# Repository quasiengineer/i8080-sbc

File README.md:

# System board for Intel 8080
FPGA-based single board computer to run Intel 8080 CPU (up to 3.125Mhz)

## Board

Full schematics in [pdf format](./pcb/schematic.pdf)

Here is shown only main part of the board:

Archive with gerber files and drill locations could be found [here](./pcb/manufacturing.zip)

Bill of material in [CSV format](./pcb/bom.csv)

|Reference                                                                                                                           |Value               |Footprint                                                 |Mouser Part Number  |Qty|
|------------------------------------------------------------------------------------------------------------------------------------|--------------------|----------------------------------------------------------|--------------------|---|
|C1,C7,C25,C57,C62                                                                                                                   |1u                  |Capacitor_SMD:C_0805_2012Metric_Pad1.18x1.45mm_HandSolder |187-CL21B105KAFNNNG |5  |
|C2,C3,C6,C11,C12,C13,C17,C18,C19,C21,C22,C23,<br>C24,C26,C28,C29,C31,C32,C33,C34,C35,C36,C37,<br>C38,C39,C40,C41,C43,C44,C46,C48,C49,C56,C58|100n                |Capacitor_SMD:C_0805_2012Metric_Pad1.18x1.45mm_HandSolder |187-CL21B104KBCNNND |34 |
|C4,C30                                                                                                                              |4u7,4u7, low-ESR    |Capacitor_SMD:C_0805_2012Metric_Pad1.18x1.45mm_HandSolder |187-CL21A475KAQNNNE |2  |
|C5,C59,C61,C64                                                                                                                      |22u                 |Capacitor_SMD:C_0805_2012Metric_Pad1.18x1.45mm_HandSolder |187-CL21A226MAYNNNE |4  |
|C8,C9,C10,C55                                                                                                                       |10u,10u, low-ESR    |Capacitor_SMD:C_0805_2012Metric_Pad1.18x1.45mm_HandSolder |187-CL21A106KAYNNNF |4  |
|C20,C27                                                                                                                             |10p                 |Capacitor_SMD:C_0805_2012Metric_Pad1.18x1.45mm_HandSolder |710-885012007051    |2  |
|C42,C45                                                                                                                             |10p                 |Capacitor_SMD:C_0402_1005Metric_Pad0.74x0.62mm_HandSolder |603-CC402JRNPO8BN100|2  |
|C60                                                                                                                                 |33p                 |Capacitor_SMD:C_0805_2012Metric_Pad1.18x1.45mm_HandSolder |710-885012007031    |1  |
|C63                                                                                                                                 |22p                 |Capacitor_SMD:C_0805_2012Metric_Pad1.18x1.45mm_HandSolder |710-885012007053    |1  |
|D1                                                                                                                                  |Red                 |LED_SMD:LED_0805_2012Metric_Pad1.15x1.40mm_HandSolder     |710-150080RS75000   |1  |
|D2                                                                                                                                  |Green               |LED_SMD:LED_0805_2012Metric_Pad1.15x1.40mm_HandSolder     |710-150080GS75000   |1  |
|FB1                                                                                                                                 |Ferrite_Bead        |Inductor_SMD:L_0805_2012Metric_Pad1.15x1.40mm_HandSolder  |652-MG2029-101Y     |1  |
|H1,H2,H3,H4                                                                                                                         |2.5mm               |MountingHole:MountingHole_2.5mm_Pad_Via                   |                    |4  |
|IC1,IC2                                                                                                                             |SN74LVC861APW       |Project components:SOP65P640X120-24N                      |595-SN74LVC861APW   |2  |
|IC5                                                                                                                                 |CD74HC243M96        |Project components:SOIC127P600X175-14N                    |595-CD74HC243M96    |1  |
|IC6                                                                                                                                 |M2GL005-TQG144I     |Project components:QFP50P2200X2200X160-144N               |494-M2GL005-TQG144I |1  |
|IC7,IC8                                                                                                                             |UCC27511DBVR        |SOT95P280X145-6N                                          |595-UCC27511DBVR    |2  |
|IC9                                                                                                                                 |TXS0108EPWRG4       |Project components:SOP65P640X120-20N                      |595-TXS0108EPWRG4   |1  |
|J1                                                                                                                                  |Type-C              |Connector_USB:USB_C_Receptacle_JAE_DX07S016JA1R1500       |656-DX07S016JA1R1500|1  |
|J2,J4                                                                                                                               |FPGA JTAG,MCU JTAG  |Connector_PinHeader_2.54mm:PinHeader_1x07_P2.54mm_Vertical|649-1012937990701BLF|2  |
|L1                                                                                                                                  |8u2, 800mA          |Inductor_SMD:L_1008_2520Metric_Pad1.43x2.20mm_HandSolder  |81-DFE252012F-8R2MP2|1  |
|L2                                                                                                                                  |27n                 |Inductor_SMD:L_0805_2012Metric_Pad1.15x1.40mm_HandSolder  |652-CE201210-27NJ   |1  |
|L3,L4                                                                                                                               |0u68, 5.5A          |Inductor_SMD:L_1008_2520Metric_Pad1.43x2.20mm_HandSolder  |652-SRP2512-R68M    |2  |
|R1,R18                                                                                                                              |10                  |Resistor_SMD:R_0805_2012Metric_Pad1.20x1.40mm_HandSolder  |603-RT0805DRE0710RL |2  |
|R2,R13,R14,R23                                                                                                                      |100k                |Resistor_SMD:R_0805_2012Metric_Pad1.20x1.40mm_HandSolder  |603-RT0805DRE07100KL|4  |
|R3,R6                                                                                                                               |30k                 |Resistor_SMD:R_0805_2012Metric_Pad1.20x1.40mm_HandSolder  |603-RT0805DRE0730KL |2  |
|R4                                                                                                                                  |4k7                 |Resistor_SMD:R_0805_2012Metric_Pad1.20x1.40mm_HandSolder  |603-RT0805FRE134K7L |1  |
|R5                                                                                                                                  |330k                |Resistor_SMD:R_0805_2012Metric_Pad1.20x1.40mm_HandSolder  |603-RT0805FRE07330KL|1  |
|R7                                                                                                                                  |2k2                 |Resistor_SMD:R_0805_2012Metric_Pad1.20x1.40mm_HandSolder  |603-RT0805FRE072K2L |1  |
|R8,R10,R19,R20,R21                                                                                                                  |10k                 |Resistor_SMD:R_0805_2012Metric_Pad1.20x1.40mm_HandSolder  |603-RT0805DRD0710KL |5  |
|R9,R11,R12                                                                                                                          |220                 |Resistor_SMD:R_0805_2012Metric_Pad1.20x1.40mm_HandSolder  |603-RT0805FRE07220RL|3  |
|R15,R16,R17                                                                                                                         |1k                  |Resistor_SMD:R_0805_2012Metric_Pad1.20x1.40mm_HandSolder  |603-RT0805FRE071KL  |3  |
|R22                                                                                                                                 |50                  |Resistor_SMD:R_0603_1608Metric_Pad0.98x0.95mm_HandSolder  |603-RT0603BRE0750RL |1  |
|R24                                                                                                                                 |158k                |Resistor_SMD:R_0805_2012Metric_Pad1.20x1.40mm_HandSolder  |603-RT0805FRE07158KL|1  |
|R25                                                                                                                                 |34k8                |Resistor_SMD:R_0805_2012Metric_Pad1.20x1.40mm_HandSolder  |603-RT0805FRE0734K8L|1  |
|R26,R27                                                                                                                             |5k1                 |Resistor_SMD:R_0805_2012Metric_Pad1.20x1.40mm_HandSolder  |603-RT0805FRE075K1L |2  |
|SW1                                                                                                                                 |BOOT_MODE           |Project components:SLW1215865AD                           |SLW-121586-5A-D     |1  |
|SW2,SW3                                                                                                                             |RESET_FPGA,RESET_MCU|Project components:435451019820                           |710-435451019820    |2  |
|U1                                                                                                                                  |8080A               |Package_DIP:DIP-40_W15.24mm                               |571-1-2199299-5     |1  |
|U2,U8                                                                                                                               |LX7167ACLD-TR       |Package_DFN_QFN:DFN-8-1EP_2x2mm_P0.5mm_EP0.8x1.6mm        |494-LX7167ACLD-TR   |2  |
|U3                                                                                                                                  |MP3438              |Package_TO_SOT_SMD:SOT-583-8                              |946-MP3438GTL-P     |1  |
|U4                                                                                                                                  |ICL7660             |Package_SO:SOIC-8_3.9x4.9mm_P1.27mm                       |968-ICL7660CBAZA-T  |1  |
|U6                                                                                                                                  |APX803-31SAG-7      |Package_TO_SOT_SMD:SOT-23-3                               |621-APX803-31SAG-7  |1  |
|U7                                                                                                                                  |STM32G4A1KEUx       |Package_DFN_QFN:QFN-32-1EP_5x5mm_P0.5mm_EP3.45x3.45mm     |511-STM32G4A1KEU6   |1  |
|Y1                                                                                                                                  |16Mhz, CL=10p       |Project components:XTAL_ECS-160-10-36-CKM-TR3             |520-160-10-36CKM-TR3|1  |
|Y2                                                                                                                                  |16Mhz               |Crystal:Crystal_SMD_2016-4Pin_2.0x1.6mm                   |81-XRCGB16M000FXN02R|1  |

## MCU Firmware

There is compiled [hex file](./firmware/bin/i8080-sbc.hex) in repository, that could be flashed to PCB.

To flash you can use your favorite JTAG probe and software by your choice.
Or you can use default stm32 bootloader that supports uploading firmware via USB - just switch BOOT switch in direction to the USB connector.

I am using ft232r-based probe and OpenOCD, you can find my config [here](./openocd_stm32.cfg).

## FPGA bitstream

Again there is compiled [bitsream](./fpga/bin/i8080-sbc.dat).
So you could flash it by using either tool from vendor like FlashPro programmer or use same ft232 board and [DirectC-based tool](https://github.com/quasiengineer/microchip-jtag-flasher-ftdi).

## Software

To upload ROM/RAM image (i8080 has same memory space for ROM and RAM) you can type:

```sh
node index.js -port="COM1" -rom="hello_world" -verify
```

If all is good terminal should looks like that:

Be aware that FPGA currently does not inform about i8080 HALT state, so controller software need to be terminated after end of i8080 program execution.

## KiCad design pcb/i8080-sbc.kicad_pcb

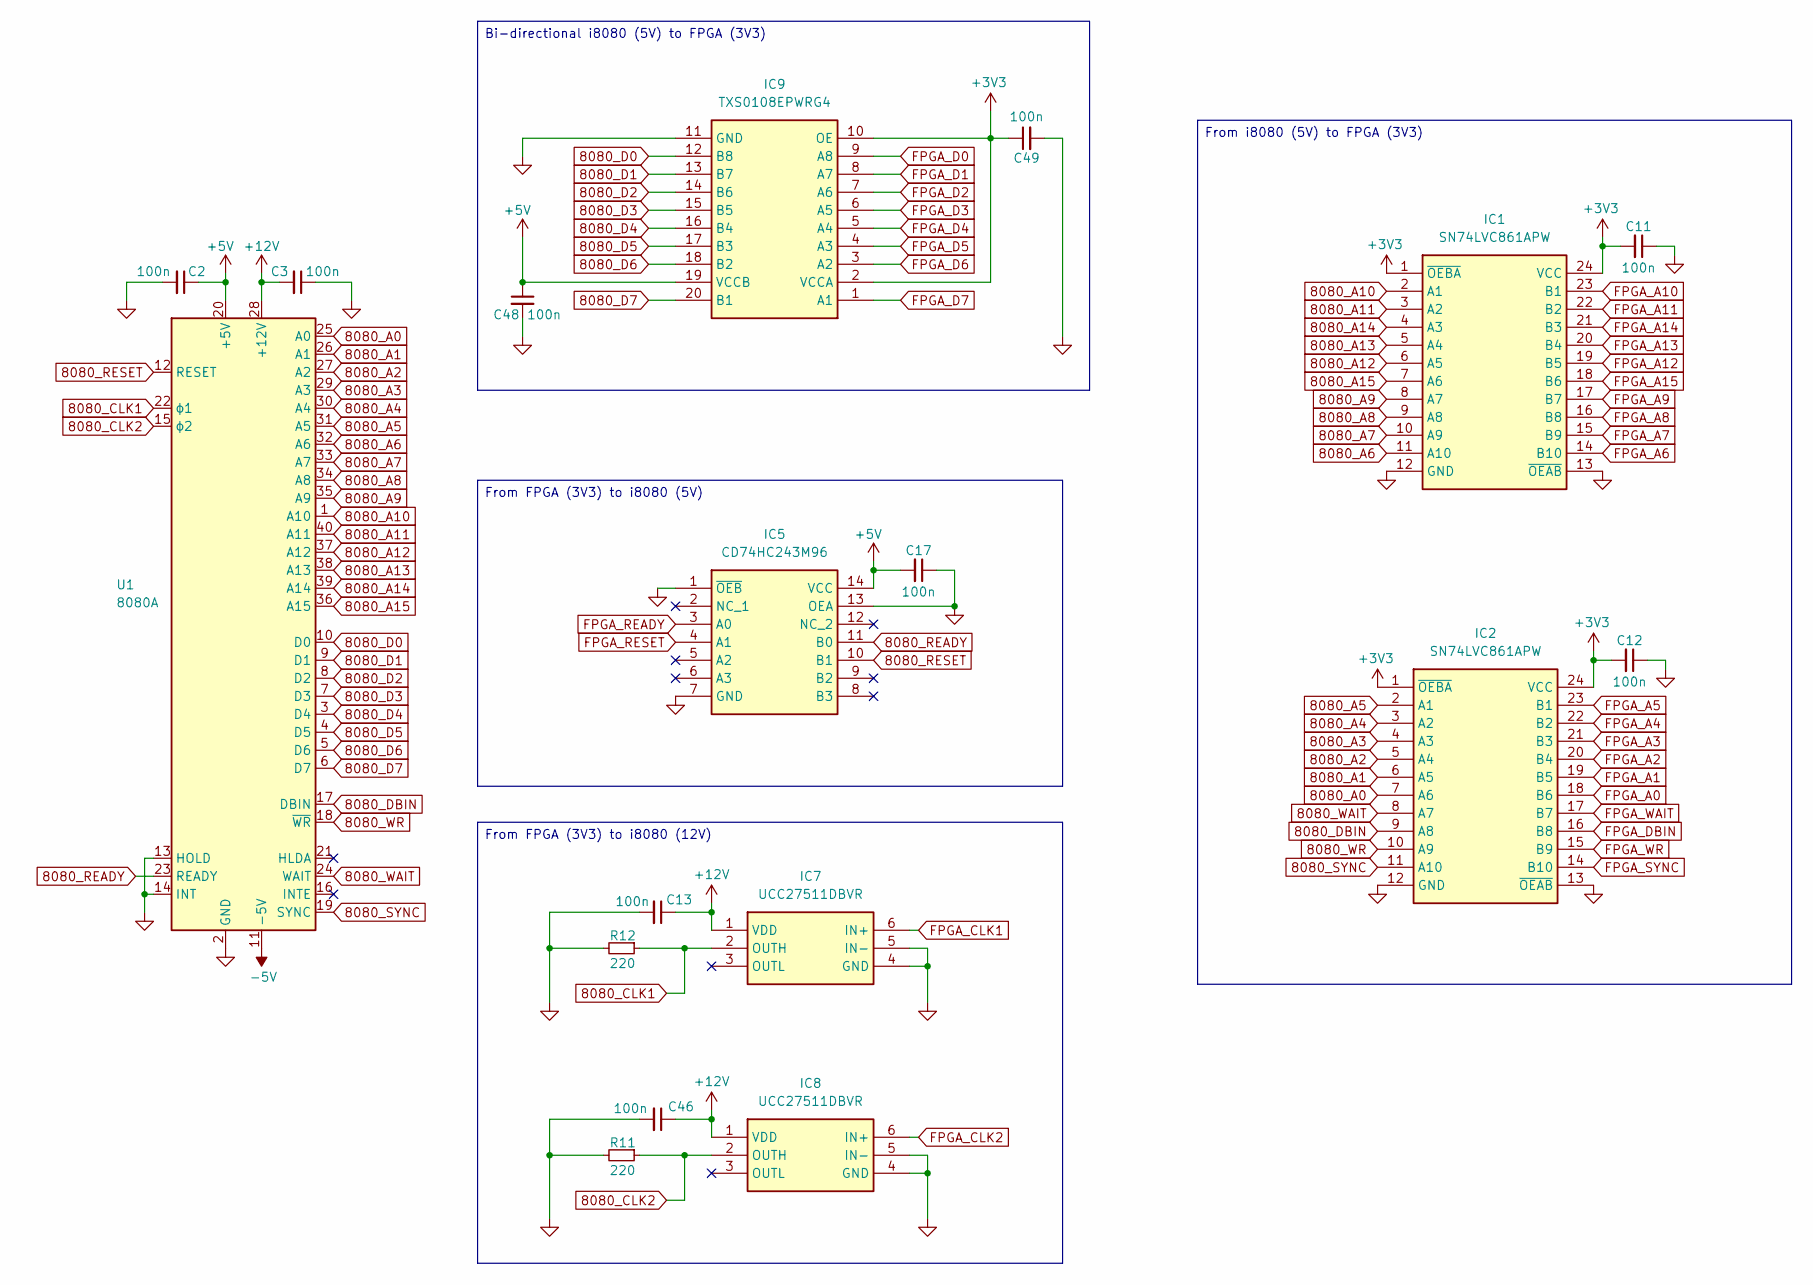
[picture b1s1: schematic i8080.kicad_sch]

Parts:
C2, C3, C11, C12, C13, C17, C46, C48, C49: 100n; C_0805_2012Metric_Pad1.18x1.45mm_HandSolder; Mouser Part Number 187-CL21B104KBCNNND
IC1, IC2: SN74LVC861APW; SOP65P640X120-24N; Mouser Part Number 595-SN74LVC861APW
IC5: CD74HC243M96; SOIC127P600X175-14N; Mouser Part Number 595-CD74HC243M96
IC7, IC8: UCC27511DBVR; SOT95P280X145-6N; Mouser Part Number 595-UCC27511DBVR
IC9: TXS0108EPWRG4; SOP65P640X120-20N; Mouser Part Number 595-TXS0108EPWRG4
R11, R12: 220; R_0805_2012Metric_Pad1.20x1.40mm_HandSolder; Mouser Part Number 603-RT0805FRE07220RL
U1: 8080A; DIP-40_W15.24mm; Mouser Part Number 571-1-2199299-5

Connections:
8080_A0: IC2.7 (A6), U1.25 (A0)
8080_A1: IC2.6 (A5), U1.26 (A1)
8080_A2: IC2.5 (A4), U1.27 (A2)
8080_A3: IC2.4 (A3), U1.29 (A3)
8080_A4: IC2.3 (A2), U1.30 (A4)
8080_A5: IC2.2 (A1), U1.31 (A5)
8080_A6: IC1.11 (A10), U1.32 (A6)
8080_A7: IC1.10 (A9), U1.33 (A7)
8080_A8: IC1.9 (A8), U1.34 (A8)
8080_A9: IC1.8 (A7), U1.35 (A9)
8080_A10: IC1.2 (A1), U1.1 (A10)
8080_A11: IC1.3 (A2), U1.40 (A11)
8080_A12: IC1.6 (A5), U1.37 (A12)
8080_A13: IC1.5 (A4), U1.38 (A13)
8080_A14: IC1.4 (A3), U1.39 (A14)
8080_A15: IC1.7 (A6), U1.36 (A15)
8080_CLK1: IC7.2 (OUTH), R12.1, U1.22 (ϕ1)
8080_CLK2: IC8.2 (OUTH), R11.1, U1.15 (ϕ2)
8080_D0: IC9.12 (B8), U1.10 (D0)
8080_D1: IC9.13 (B7), U1.9 (D1)
8080_D2: IC9.14 (B6), U1.8 (D2)
8080_D3: IC9.15 (B5), U1.7 (D3)
8080_D4: IC9.16 (B4), U1.3 (D4)
8080_D5: IC9.17 (B3), U1.4 (D5)
8080_D6: IC9.18 (B2), U1.5 (D6)
8080_D7: IC9.20 (B1), U1.6 (D7)
8080_DBIN: IC2.9 (A8), U1.17 (DBIN)
8080_READY: IC5.11 (B0), U1.23 (READY)
8080_RESET: IC5.10 (B1), U1.12 (RESET)
8080_SYNC: IC2.11 (A10), U1.19 (SYNC)
8080_WAIT: IC2.8 (A7), U1.24 (WAIT)
8080_WR: IC2.10 (A9), U1.18 (~WR)
+3V3: C11.2, C12.2, C49.1, IC1.1 (~OEBA), IC1.24 (VCC), IC2.1 (~OEBA), IC2.24 (VCC), IC9.2 (VCCA), IC9.10 (OE); also elsewhere on the board
+5V: C2.1, C17.2, C48.1, IC5.14 (VCC), IC9.19 (VCCB), U1.20 (+5V); also elsewhere on the board
+12V: C3.2, C13.1, C46.1, IC7.1 (VDD), IC8.1 (VDD), U1.28 (+12V); also elsewhere on the board
-5V: U1.11 (-5V); also elsewhere on the board
FPGA_A0: IC2.18 (B6); also elsewhere on the board
FPGA_A1: IC2.19 (B5); also elsewhere on the board
FPGA_A2: IC2.20 (B4); also elsewhere on the board
FPGA_A3: IC2.21 (B3); also elsewhere on the board
FPGA_A4: IC2.22 (B2); also elsewhere on the board
FPGA_A5: IC2.23 (B1); also elsewhere on the board
FPGA_A6: IC1.14 (B10); also elsewhere on the board
FPGA_A7: IC1.15 (B9); also elsewhere on the board
FPGA_A8: IC1.16 (B8); also elsewhere on the board
FPGA_A9: IC1.17 (B7); also elsewhere on the board
FPGA_A10: IC1.23 (B1); also elsewhere on the board
FPGA_A11: IC1.22 (B2); also elsewhere on the board
FPGA_A12: IC1.19 (B5); also elsewhere on the board
FPGA_A13: IC1.20 (B4); also elsewhere on the board
FPGA_A14: IC1.21 (B3); also elsewhere on the board
FPGA_A15: IC1.18 (B6); also elsewhere on the board
FPGA_CLK1: IC7.6 (IN+); also elsewhere on the board
FPGA_CLK2: IC8.6 (IN+); also elsewhere on the board
FPGA_D0: IC9.9 (A8); also elsewhere on the board
FPGA_D1: IC9.8 (A7); also elsewhere on the board
FPGA_D2: IC9.7 (A6); also elsewhere on the board
FPGA_D3: IC9.6 (A5); also elsewhere on the board
FPGA_D4: IC9.5 (A4); also elsewhere on the board
FPGA_D5: IC9.4 (A3); also elsewhere on the board
FPGA_D6: IC9.3 (A2); also elsewhere on the board
FPGA_D7: IC9.1 (A1); also elsewhere on the board
FPGA_DBIN: IC2.16 (B8); also elsewhere on the board
FPGA_READY: IC5.3 (A0); also elsewhere on the board
FPGA_RESET: IC5.4 (A1); also elsewhere on the board
FPGA_SYNC: IC2.14 (B10); also elsewhere on the board
FPGA_WAIT: IC2.17 (B7); also elsewhere on the board
FPGA_WR: IC2.15 (B9); also elsewhere on the board
GND: C2.2, C3.1, C11.1, C12.1, C13.2, C17.1, C46.2, C48.2, C49.2, IC1.12 (GND), IC1.13 (~OEAB), IC2.12 (GND), IC2.13 (~OEAB), IC5.1 (~OEB), IC5.7 (GND), IC5.13 (OEA), IC7.4 (GND), IC7.5 (IN-), IC8.4 (GND), IC8.5 (IN-), IC9.11 (GND), R11.2, R12.2, U1.2 (GND), U1.13 (HOLD), U1.14 (INT); also elsewhere on the board

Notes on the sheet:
From FPGA (3V3) to i8080 (12V)
From i8080 (5V) to FPGA (3V3)
Bi-directional i8080 (5V) to FPGA (3V3)
From FPGA (3V3) to i8080 (5V)

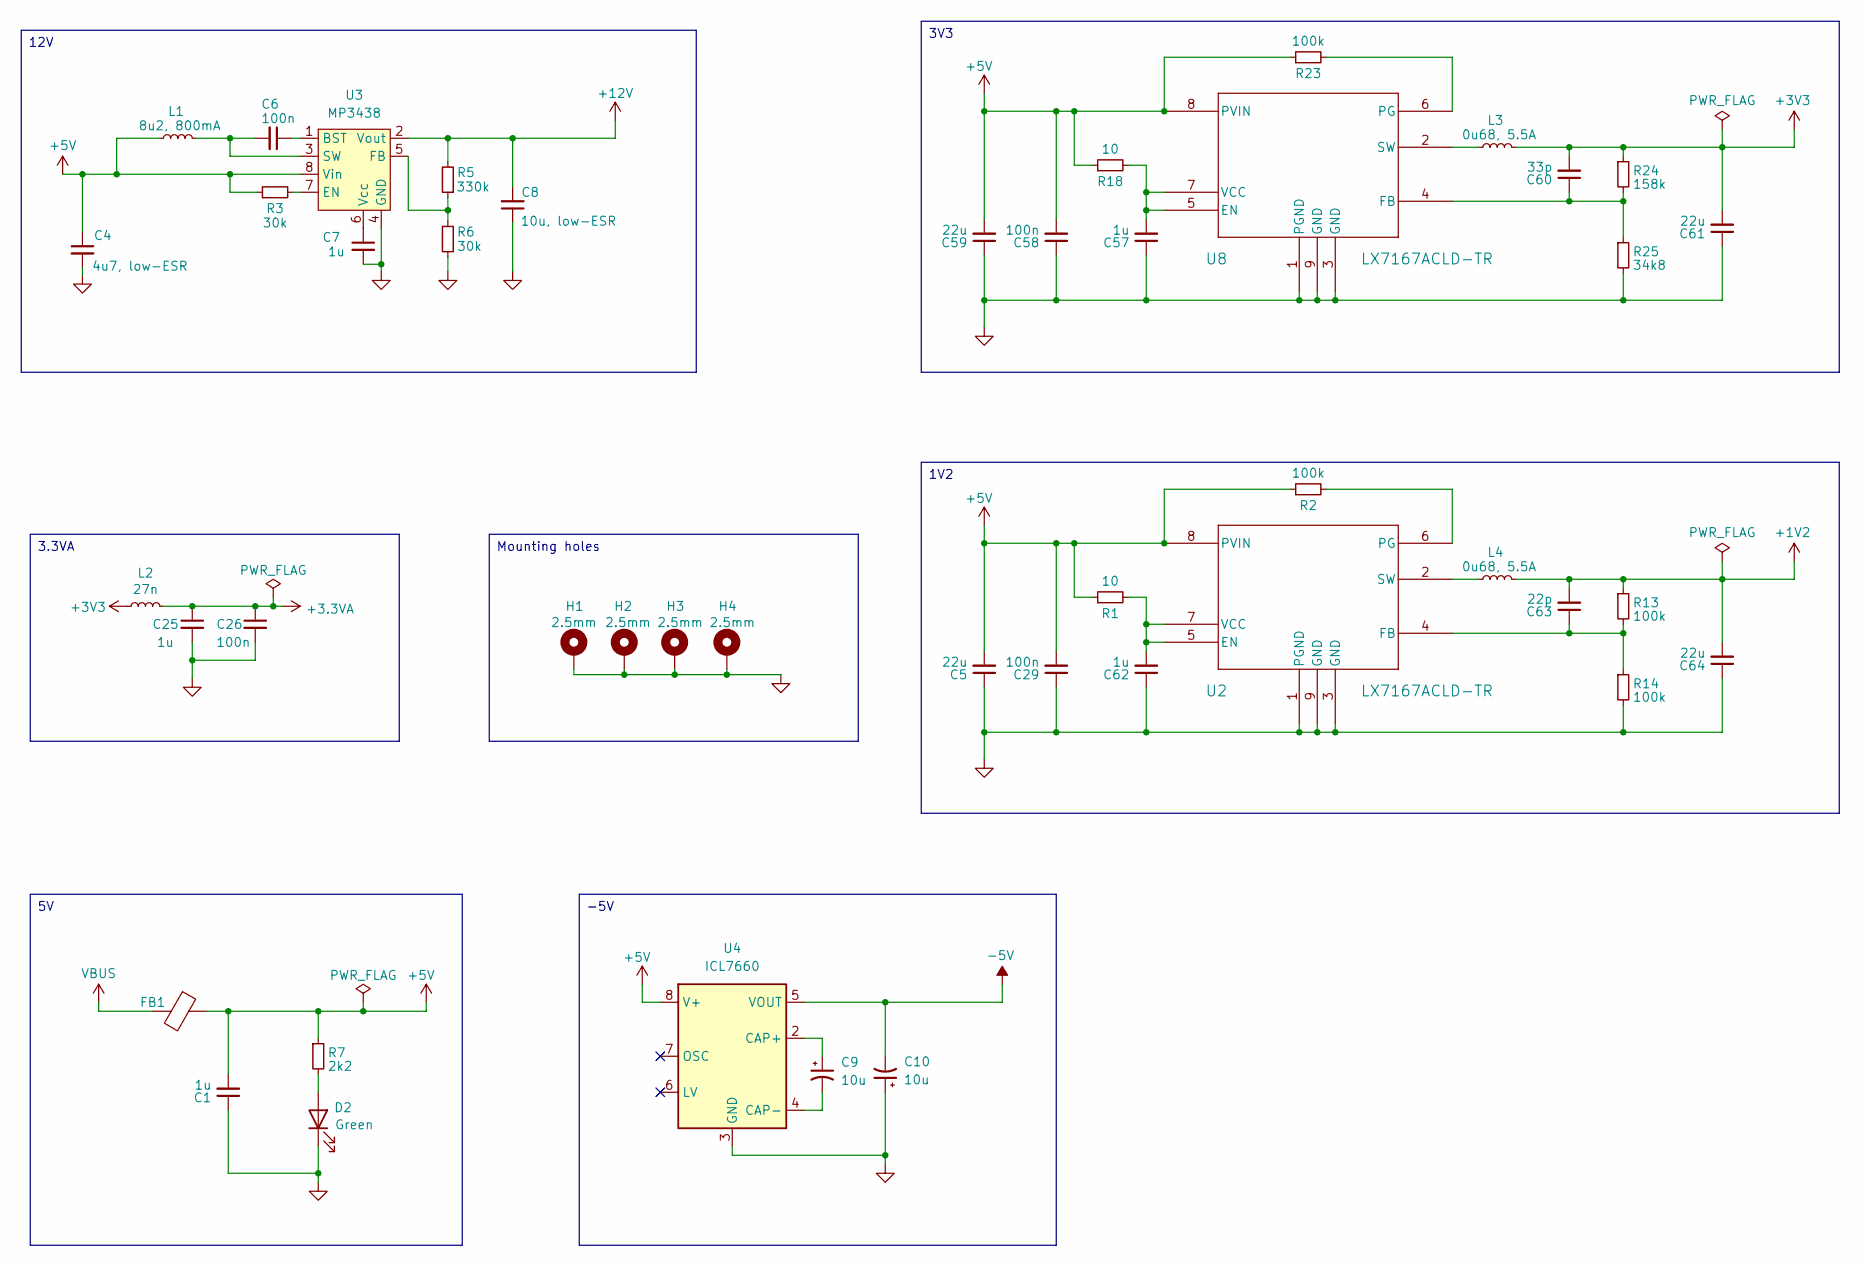
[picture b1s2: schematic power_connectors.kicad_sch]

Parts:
C1, C7, C25, C57, C62: 1u; C_0805_2012Metric_Pad1.18x1.45mm_HandSolder; Mouser Part Number 187-CL21B105KAFNNNG
C4: 4u7, low-ESR; C_0805_2012Metric_Pad1.18x1.45mm_HandSolder; Mouser Part Number 187-CL21A475KAQNNNE
C5, C59, C61, C64: 22u; C_0805_2012Metric_Pad1.18x1.45mm_HandSolder; Mouser Part Number 187-CL21A226MAYNNNE
C6, C26, C29, C58: 100n; C_0805_2012Metric_Pad1.18x1.45mm_HandSolder; Mouser Part Number 187-CL21B104KBCNNND
C8: 10u, low-ESR; C_0805_2012Metric_Pad1.18x1.45mm_HandSolder; Mouser Part Number 187-CL21A106KAYNNNF
C9, C10: 10u; C_0805_2012Metric_Pad1.18x1.45mm_HandSolder; Mouser Part Number 187-CL21A106KAYNNNF
C60: 33p; C_0805_2012Metric_Pad1.18x1.45mm_HandSolder; Mouser Part Number 710-885012007031
C63: 22p; C_0805_2012Metric_Pad1.18x1.45mm_HandSolder; Mouser Part Number 710-885012007053
D2: Green; LED_0805_2012Metric_Pad1.15x1.40mm_HandSolder; Mouser Part Number 710-150080GS75000
FB1: Ferrite_Bead; L_0805_2012Metric_Pad1.15x1.40mm_HandSolder; Mouser Part Number 652-MG2029-101Y
H1, H2, H3, H4: 2.5mm; MountingHole_2.5mm_Pad_Via
L1: 8u2, 800mA; L_1008_2520Metric_Pad1.43x2.20mm_HandSolder; Mouser Part Number 81-DFE252012F-8R2MP2
L2: 27n; L_0805_2012Metric_Pad1.15x1.40mm_HandSolder; Mouser Part Number 652-CE201210-27NJ
L3, L4: 0u68, 5.5A; L_1008_2520Metric_Pad1.43x2.20mm_HandSolder; Mouser Part Number 652-SRP2512-R68M
R1, R18: 10; R_0805_2012Metric_Pad1.20x1.40mm_HandSolder; Mouser Part Number 603-RT0805DRE0710RL
R2, R13, R14, R23: 100k; R_0805_2012Metric_Pad1.20x1.40mm_HandSolder; Mouser Part Number 603-RT0805DRE07100KL
R3, R6: 30k; R_0805_2012Metric_Pad1.20x1.40mm_HandSolder; Mouser Part Number 603-RT0805DRE0730KL
R5: 330k; R_0805_2012Metric_Pad1.20x1.40mm_HandSolder; Mouser Part Number 603-RT0805FRE07330KL
R7: 2k2; R_0805_2012Metric_Pad1.20x1.40mm_HandSolder; Mouser Part Number 603-RT0805FRE072K2L
R24: 158k; R_0805_2012Metric_Pad1.20x1.40mm_HandSolder; Mouser Part Number 603-RT0805FRE07158KL
R25: 34k8; R_0805_2012Metric_Pad1.20x1.40mm_HandSolder; Mouser Part Number 603-RT0805FRE0734K8L
U2, U8: LX7167ACLD-TR; DFN-8-1EP_2x2mm_P0.5mm_EP0.8x1.6mm; Mouser Part Number 494-LX7167ACLD-TR
U3: MP3438; SOT-583-8; Mouser Part Number 946-MP3438GTL-P
U4: ICL7660; SOIC-8_3.9x4.9mm_P1.27mm; Mouser Part Number 968-ICL7660CBAZA-T

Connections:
+1V2: C63.2, C64.2, L4.2, R13.1; also elsewhere on the board
+3.3VA: C25.1, C26.1, L2.2; also elsewhere on the board
+3V3: C60.2, C61.2, L2.1, L3.2, R24.1; also elsewhere on the board
+5V: C1.2, C4.1, C5.2, C29.2, C58.2, C59.2, FB1.1, L1.1, R1.1, R2.1, R3.1, R7.1, R18.1, R23.1, U2.8 (PVIN), U3.8 (Vin), U4.8 (V+), U8.8 (PVIN); also elsewhere on the board
+12V: C8.2, R5.2, U3.2 (Vout); also elsewhere on the board
-5V: C10.2, U4.5 (VOUT); also elsewhere on the board
GND: C1.1, C4.2, C5.1, C7.2, C8.1, C10.1, C25.2, C26.2, C29.1, C57.1, C58.1, C59.1, C61.1, C62.1, C64.1, D2.1 (K), H1.1, H2.1, H3.1, H4.1, R6.2, R14.2, R25.2, U2.1 (PGND), U2.3 (GND), U2.9 (GND), U3.4 (GND), U4.3 (GND), U8.1 (PGND), U8.3 (GND), U8.9 (GND); also elsewhere on the board
unnamed: D2.2 (A), R7.2
unnamed: C62.2, R1.2, U2.5 (EN), U2.7 (VCC)
unnamed: C63.1, R13.2, R14.1, U2.4 (FB)
unnamed: R2.2, U2.6 (PG)
unnamed: L4.1, U2.2 (SW)
unnamed: C6.1, U3.1 (BST)
unnamed: R3.2, U3.7 (EN)
unnamed: R5.1, R6.1, U3.5 (FB)
unnamed: C6.2, L1.2, U3.3 (SW)
unnamed: C7.1, U3.6 (Vcc)
unnamed: C9.1, U4.2 (CAP+)
unnamed: C9.2, U4.4 (CAP-)
unnamed: C57.2, R18.2, U8.5 (EN), U8.7 (VCC)
unnamed: C60.1, R24.2, R25.1, U8.4 (FB)
unnamed: R23.2, U8.6 (PG)
unnamed: L3.1, U8.2 (SW)
VBUS: FB1.2; also elsewhere on the board

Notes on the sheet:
12V
-5V
3.3VA
3V3
1V2
Mounting holes

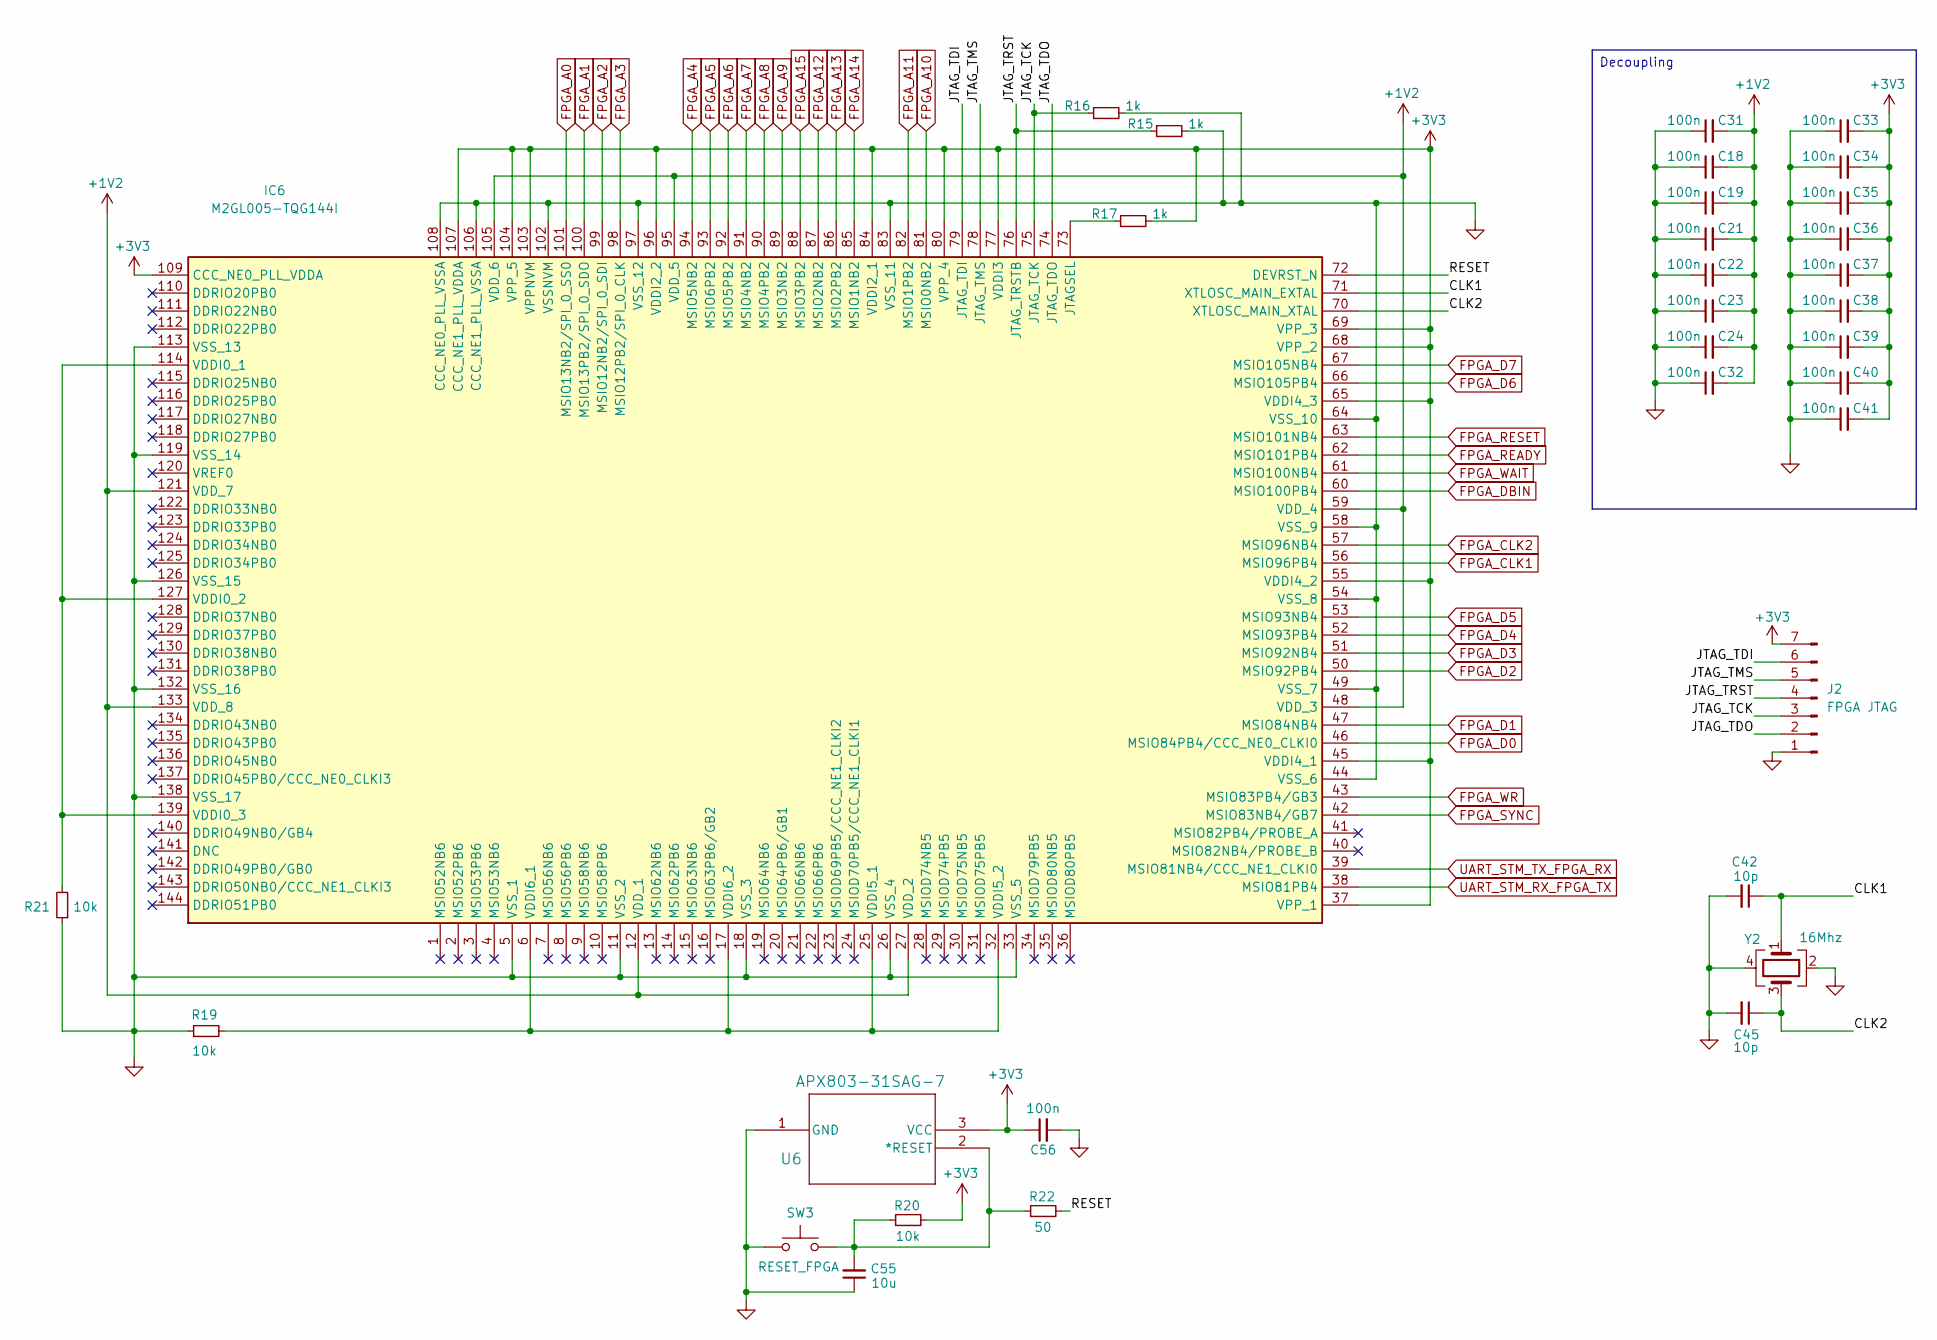
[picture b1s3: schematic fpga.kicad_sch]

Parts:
C18, C19, C21, C22, C23, C24, C31, C32, C33, C34, C35, C36, C37, C38, C39, C40, C41, C56: 100n; C_0805_2012Metric_Pad1.18x1.45mm_HandSolder; Mouser Part Number 187-CL21B104KBCNNND
C42, C45: 10p; C_0402_1005Metric_Pad0.74x0.62mm_HandSolder; Mouser Part Number 603-CC402JRNPO8BN100
C55: 10u; C_0805_2012Metric_Pad1.18x1.45mm_HandSolder; Mouser Part Number 187-CL21A106KAYNNNF
IC6: M2GL005-TQG144I; QFP50P2200X2200X160-144N; Mouser Part Number 494-M2GL005-TQG144I
J2: FPGA JTAG; PinHeader_1x07_P2.54mm_Vertical; Mouser Part Number 649-1012937990701BLF
R15, R16, R17: 1k; R_0805_2012Metric_Pad1.20x1.40mm_HandSolder; Mouser Part Number 603-RT0805FRE071KL
R19, R20, R21: 10k; R_0805_2012Metric_Pad1.20x1.40mm_HandSolder; Mouser Part Number 603-RT0805DRD0710KL
R22: 50; R_0603_1608Metric_Pad0.98x0.95mm_HandSolder; Mouser Part Number 603-RT0603BRE0750RL
SW3: RESET_FPGA; 435451019820; Mouser Part Number 710-435451019820
U6: APX803-31SAG-7; SOT-23-3; Mouser Part Number 621-APX803-31SAG-7
Y2: 16Mhz; Crystal_SMD_2016-4Pin_2.0x1.6mm; Mouser Part Number 81-XRCGB16M000FXN02R

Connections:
+1V2: C18.2, C19.2, C21.2, C22.2, C23.2, C24.2, C31.2, C32.2, IC6.12 (VDD_1), IC6.27 (VDD_2), IC6.48 (VDD_3), IC6.59 (VDD_4), IC6.95 (VDD_5), IC6.105 (VDD_6), IC6.121 (VDD_7), IC6.133 (VDD_8); also elsewhere on the board
+3V3: C33.2, C34.2, C35.2, C36.2, C37.2, C38.2, C39.2, C40.2, C41.2, C56.1, IC6.37 (VPP_1), IC6.45 (VDDI4_1), IC6.55 (VDDI4_2), IC6.65 (VDDI4_3), IC6.68 (VPP_2), IC6.69 (VPP_3), IC6.77 (VDDI3), IC6.80 (VPP_4), IC6.84 (VDDI2_1), IC6.96 (VDDI2_2), IC6.103 (VPPNVM), IC6.104 (VPP_5), IC6.107 (CCC_NE1_PLL_VDDA), IC6.109 (CCC_NE0_PLL_VDDA), J2.7, R17.2, R20.2, U6.3 (VCC); also elsewhere on the board
/FPGA/CLK1: C42.1, IC6.71 (XTLOSC_MAIN_EXTAL), Y2.1
/FPGA/CLK2: C45.1, IC6.70 (XTLOSC_MAIN_XTAL), Y2.3
/FPGA/JTAG_TCK: IC6.75 (JTAG_TCK), J2.3, R16.1
/FPGA/JTAG_TDI: IC6.79 (JTAG_TDI), J2.6
/FPGA/JTAG_TDO: IC6.74 (JTAG_TDO), J2.2
/FPGA/JTAG_TMS: IC6.78 (JTAG_TMS), J2.5
/FPGA/JTAG_TRST: IC6.76 (JTAG_TRSTB), J2.4, R15.1
/FPGA/RESET: IC6.72 (DEVRST_N), R22.2
FPGA_A0: IC6.101 (MSIO13NB2/SPI_0_SS0); also elsewhere on the board
FPGA_A1: IC6.100 (MSIO13PB2/SPI_0_SDO); also elsewhere on the board
FPGA_A2: IC6.99 (MSIO12NB2/SPI_0_SDI); also elsewhere on the board
FPGA_A3: IC6.98 (MSIO12PB2/SPI_0_CLK); also elsewhere on the board
FPGA_A4: IC6.94 (MSIO5NB2); also elsewhere on the board
FPGA_A5: IC6.93 (MSIO6PB2); also elsewhere on the board
FPGA_A6: IC6.92 (MSIO5PB2); also elsewhere on the board
FPGA_A7: IC6.91 (MSIO4NB2); also elsewhere on the board
FPGA_A8: IC6.90 (MSIO4PB2); also elsewhere on the board
FPGA_A9: IC6.89 (MSIO3NB2); also elsewhere on the board
FPGA_A10: IC6.81 (MSIO0NB2); also elsewhere on the board
FPGA_A11: IC6.82 (MSIO1PB2); also elsewhere on the board
FPGA_A12: IC6.87 (MSIO2NB2); also elsewhere on the board
FPGA_A13: IC6.86 (MSIO2PB2); also elsewhere on the board
FPGA_A14: IC6.85 (MSIO1NB2); also elsewhere on the board
FPGA_A15: IC6.88 (MSIO3PB2); also elsewhere on the board
FPGA_CLK1: IC6.56 (MSIO96PB4); also elsewhere on the board
FPGA_CLK2: IC6.57 (MSIO96NB4); also elsewhere on the board
FPGA_D0: IC6.46 (MSIO84PB4/CCC_NE0_CLKI0); also elsewhere on the board
FPGA_D1: IC6.47 (MSIO84NB4); also elsewhere on the board
FPGA_D2: IC6.50 (MSIO92PB4); also elsewhere on the board
FPGA_D3: IC6.51 (MSIO92NB4); also elsewhere on the board
FPGA_D4: IC6.52 (MSIO93PB4); also elsewhere on the board
FPGA_D5: IC6.53 (MSIO93NB4); also elsewhere on the board
FPGA_D6: IC6.66 (MSIO105PB4); also elsewhere on the board
FPGA_D7: IC6.67 (MSIO105NB4); also elsewhere on the board
FPGA_DBIN: IC6.60 (MSIO100PB4); also elsewhere on the board
FPGA_READY: IC6.62 (MSIO101PB4); also elsewhere on the board
FPGA_RESET: IC6.63 (MSIO101NB4); also elsewhere on the board
FPGA_SYNC: IC6.42 (MSIO83NB4/GB7); also elsewhere on the board
FPGA_WAIT: IC6.61 (MSIO100NB4); also elsewhere on the board
FPGA_WR: IC6.43 (MSIO83PB4/GB3); also elsewhere on the board
GND: C18.1, C19.1, C21.1, C22.1, C23.1, C24.1, C31.1, C32.1, C33.1, C34.1, C35.1, C36.1, C37.1, C38.1, C39.1, C40.1, C41.1, C42.2, C45.2, C55.1, C56.2, IC6.5 (VSS_1), IC6.11 (VSS_2), IC6.18 (VSS_3), IC6.26 (VSS_4), IC6.33 (VSS_5), IC6.44 (VSS_6), IC6.49 (VSS_7), IC6.54 (VSS_8), IC6.58 (VSS_9), IC6.64 (VSS_10), IC6.83 (VSS_11), IC6.97 (VSS_12), IC6.102 (VSSNVM), IC6.106 (CCC_NE1_PLL_VSSA), IC6.108 (CCC_NE0_PLL_VSSA), IC6.113 (VSS_13), IC6.119 (VSS_14), IC6.126 (VSS_15), IC6.132 (VSS_16), IC6.138 (VSS_17), J2.1, R15.2, R16.2, R19.1, R21.1, SW3.1, U6.1 (GND), Y2.2, Y2.4; also elsewhere on the board
unnamed: IC6.73 (JTAGSEL), R17.1
unnamed: IC6.114 (VDDI0_1), IC6.127 (VDDI0_2), IC6.139 (VDDI0_3), R21.2
unnamed: IC6.6 (VDDI6_1), IC6.17 (VDDI6_2), IC6.25 (VDDI5_1), IC6.32 (VDDI5_2), R19.2
unnamed: C55.2, R20.1, R22.1, SW3.2, U6.2 (*RESET)
UART_STM_RX_FPGA_TX: IC6.38 (MSIO81PB4); also elsewhere on the board
UART_STM_TX_FPGA_RX: IC6.39 (MSIO81NB4/CCC_NE1_CLKI0); also elsewhere on the board

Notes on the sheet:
Decoupling

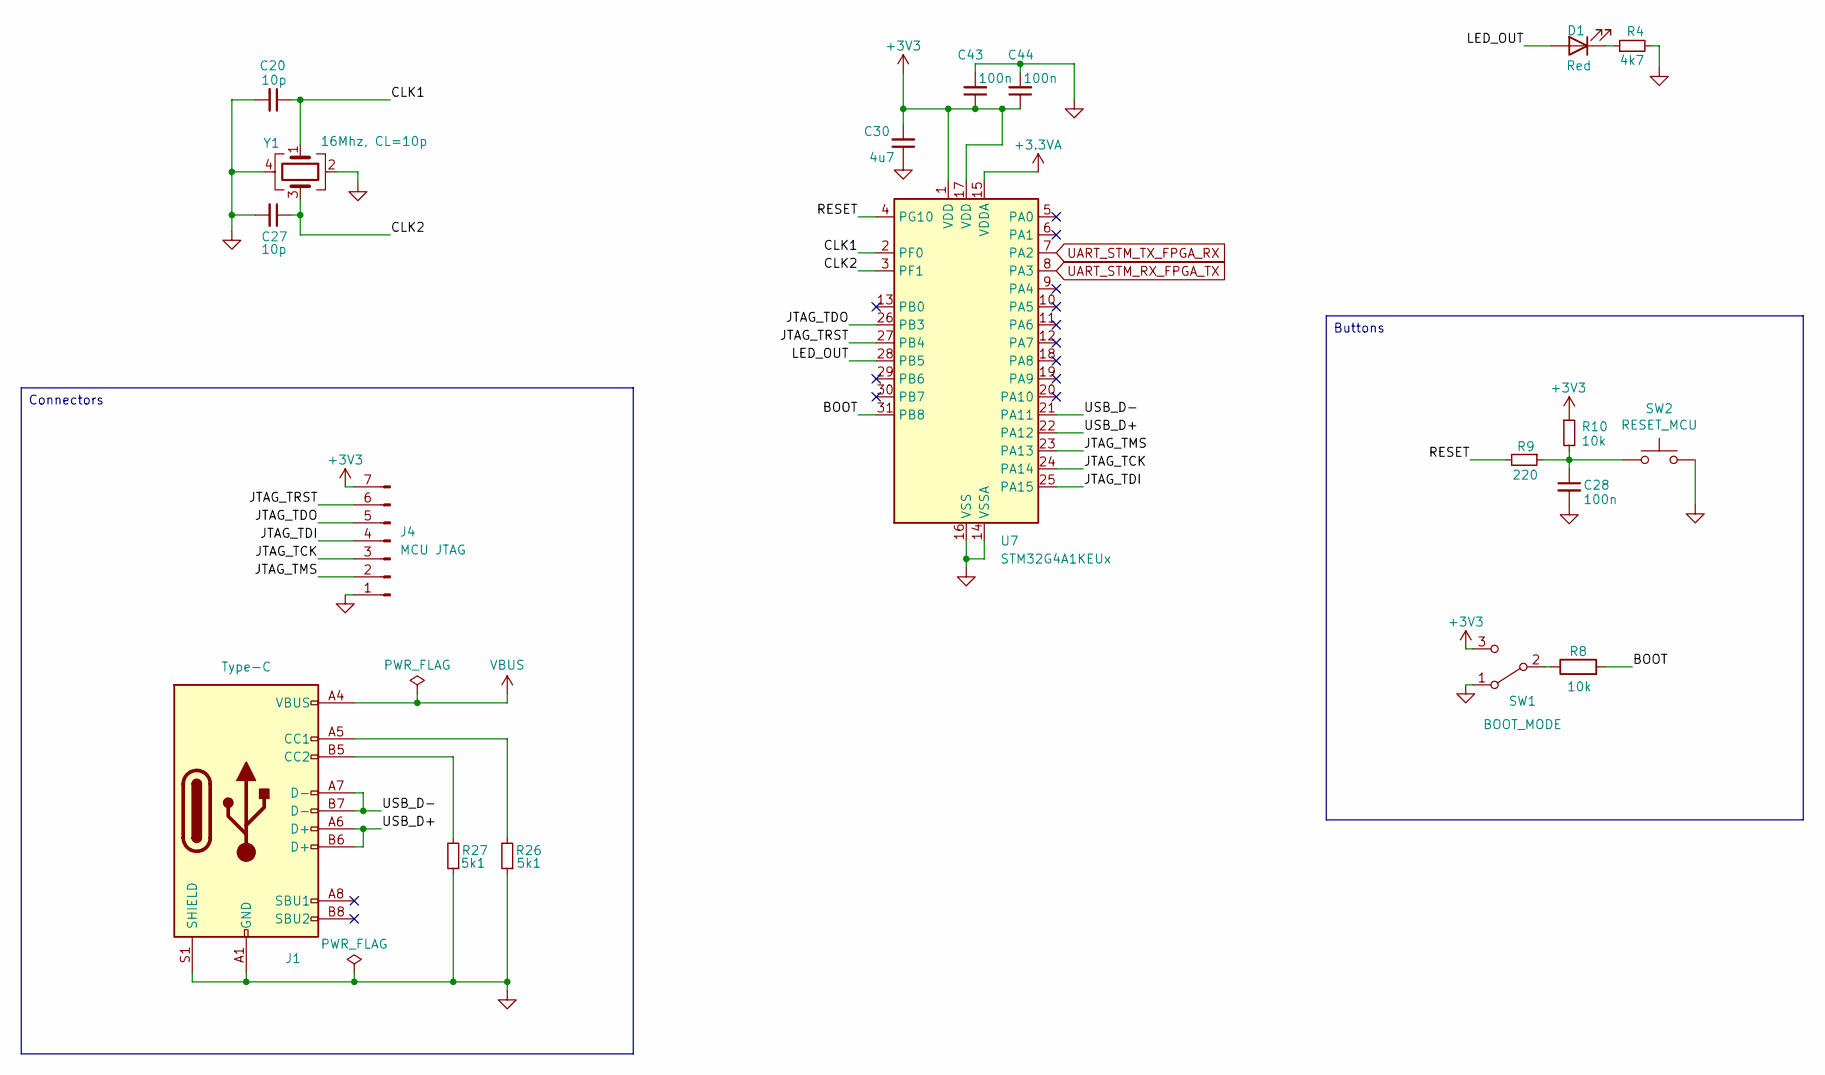
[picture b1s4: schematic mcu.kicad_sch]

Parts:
C20, C27: 10p; C_0805_2012Metric_Pad1.18x1.45mm_HandSolder; Mouser Part Number 710-885012007051
C28, C43, C44: 100n; C_0805_2012Metric_Pad1.18x1.45mm_HandSolder; Mouser Part Number 187-CL21B104KBCNNND
C30: 4u7; C_0805_2012Metric_Pad1.18x1.45mm_HandSolder; Mouser Part Number 187-CL21A475KAQNNNE
D1: Red; LED_0805_2012Metric_Pad1.15x1.40mm_HandSolder; Mouser Part Number 710-150080RS75000
J1: Type-C; USB_C_Receptacle_JAE_DX07S016JA1R1500; Mouser Part Number 656-DX07S016JA1R1500
J4: MCU JTAG; PinHeader_1x07_P2.54mm_Vertical; Mouser Part Number 649-1012937990701BLF
R4: 4k7; R_0805_2012Metric_Pad1.20x1.40mm_HandSolder; Mouser Part Number 603-RT0805FRE134K7L
R8, R10: 10k; R_0805_2012Metric_Pad1.20x1.40mm_HandSolder; Mouser Part Number 603-RT0805DRD0710KL
R9: 220; R_0805_2012Metric_Pad1.20x1.40mm_HandSolder; Mouser Part Number 603-RT0805FRE07220RL
R26, R27: 5k1; R_0805_2012Metric_Pad1.20x1.40mm_HandSolder; Mouser Part Number 603-RT0805FRE075K1L
SW1: BOOT_MODE; SLW1215865AD; Mouser Part Number SLW-121586-5A-D
SW2: RESET_MCU; 435451019820; Mouser Part Number 710-435451019820
U7: STM32G4A1KEUx; QFN-32-1EP_5x5mm_P0.5mm_EP3.45x3.45mm; Mouser Part Number 511-STM32G4A1KEU6
Y1: 16Mhz, CL=10p; XTAL_ECS-160-10-36-CKM-TR3; Mouser Part Number 520-160-10-36CKM-TR3

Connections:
+3.3VA: U7.15 (VDDA); also elsewhere on the board
+3V3: C30.2, C43.1, C44.1, J4.7, R10.1, SW1.3 (C), U7.1 (VDD), U7.17 (VDD); also elsewhere on the board
/MCU/BOOT: R8.2, U7.31 (PB8)
/MCU/CLK1: C20.1, U7.2 (PF0), Y1.1
/MCU/CLK2: C27.1, U7.3 (PF1), Y1.3
/MCU/JTAG_TCK: J4.3, U7.24 (PA14)
/MCU/JTAG_TDI: J4.4, U7.25 (PA15)
/MCU/JTAG_TDO: J4.5, U7.26 (PB3)
/MCU/JTAG_TMS: J4.2, U7.23 (PA13)
/MCU/JTAG_TRST: J4.6, U7.27 (PB4)
/MCU/LED_OUT: D1.2 (A), U7.28 (PB5)
/MCU/RESET: R9.2, U7.4 (PG10)
/MCU/USB_D+: J1.A6 (D+), J1.B6 (D+), U7.22 (PA12)
/MCU/USB_D-: J1.A7 (D-), J1.B7 (D-), U7.21 (PA11)
GND: C20.2, C27.2, C28.2, C30.1, C43.2, C44.2, J1.A1 (GND), J1.A12 (GND), J1.B1 (GND), J1.B12 (GND), J1.S1 (SHIELD), J4.1, R4.2, R26.1, R27.1, SW1.1 (A), SW2.2, U7.14 (VSSA), U7.16 (VSS), U7.32 (VSS), U7.33 (VSS), Y1.2, Y1.4; also elsewhere on the board
unnamed: C28.1, R9.1, R10.2, SW2.1
unnamed: D1.1 (K), R4.1
unnamed: J1.A5 (CC1), R26.2
unnamed: J1.B5 (CC2), R27.2
unnamed: R8.1, SW1.2 (B)
UART_STM_RX_FPGA_TX: U7.8 (PA3); also elsewhere on the board
UART_STM_TX_FPGA_RX: U7.7 (PA2); also elsewhere on the board
VBUS: J1.A4 (VBUS), J1.A9 (VBUS), J1.B4 (VBUS), J1.B9 (VBUS); also elsewhere on the board

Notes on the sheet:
Buttons
Connectors
